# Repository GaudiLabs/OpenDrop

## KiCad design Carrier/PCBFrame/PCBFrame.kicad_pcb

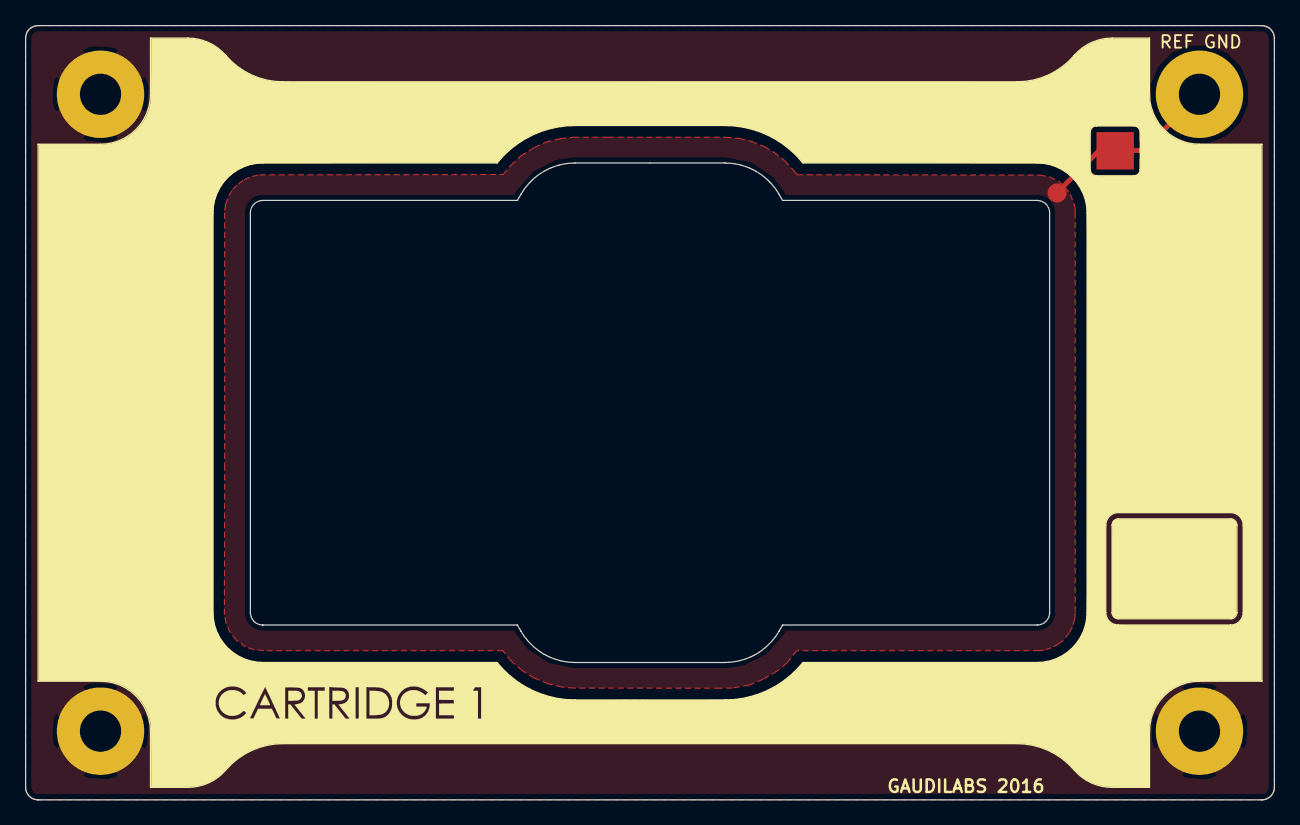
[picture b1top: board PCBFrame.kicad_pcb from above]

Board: 2 copper layers, 100.0 x 62.0 mm, 6 parts (0 on the bottom side), 2 nets.

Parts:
REF GND: MountPad3; MountingHoleRound3mm
X2, X3, X4: MountPad3; MountingHoleRound3mm
X5: MountPad3; Measurement_Point_Round-SMD-Pad_Small
X6: MountPad3; Measurement_Point_Square-SMD-Pad_Big

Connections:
GND: X2.1, X3.1, X4.1
GNDREF: REF GND.1, X5.1, X6.1

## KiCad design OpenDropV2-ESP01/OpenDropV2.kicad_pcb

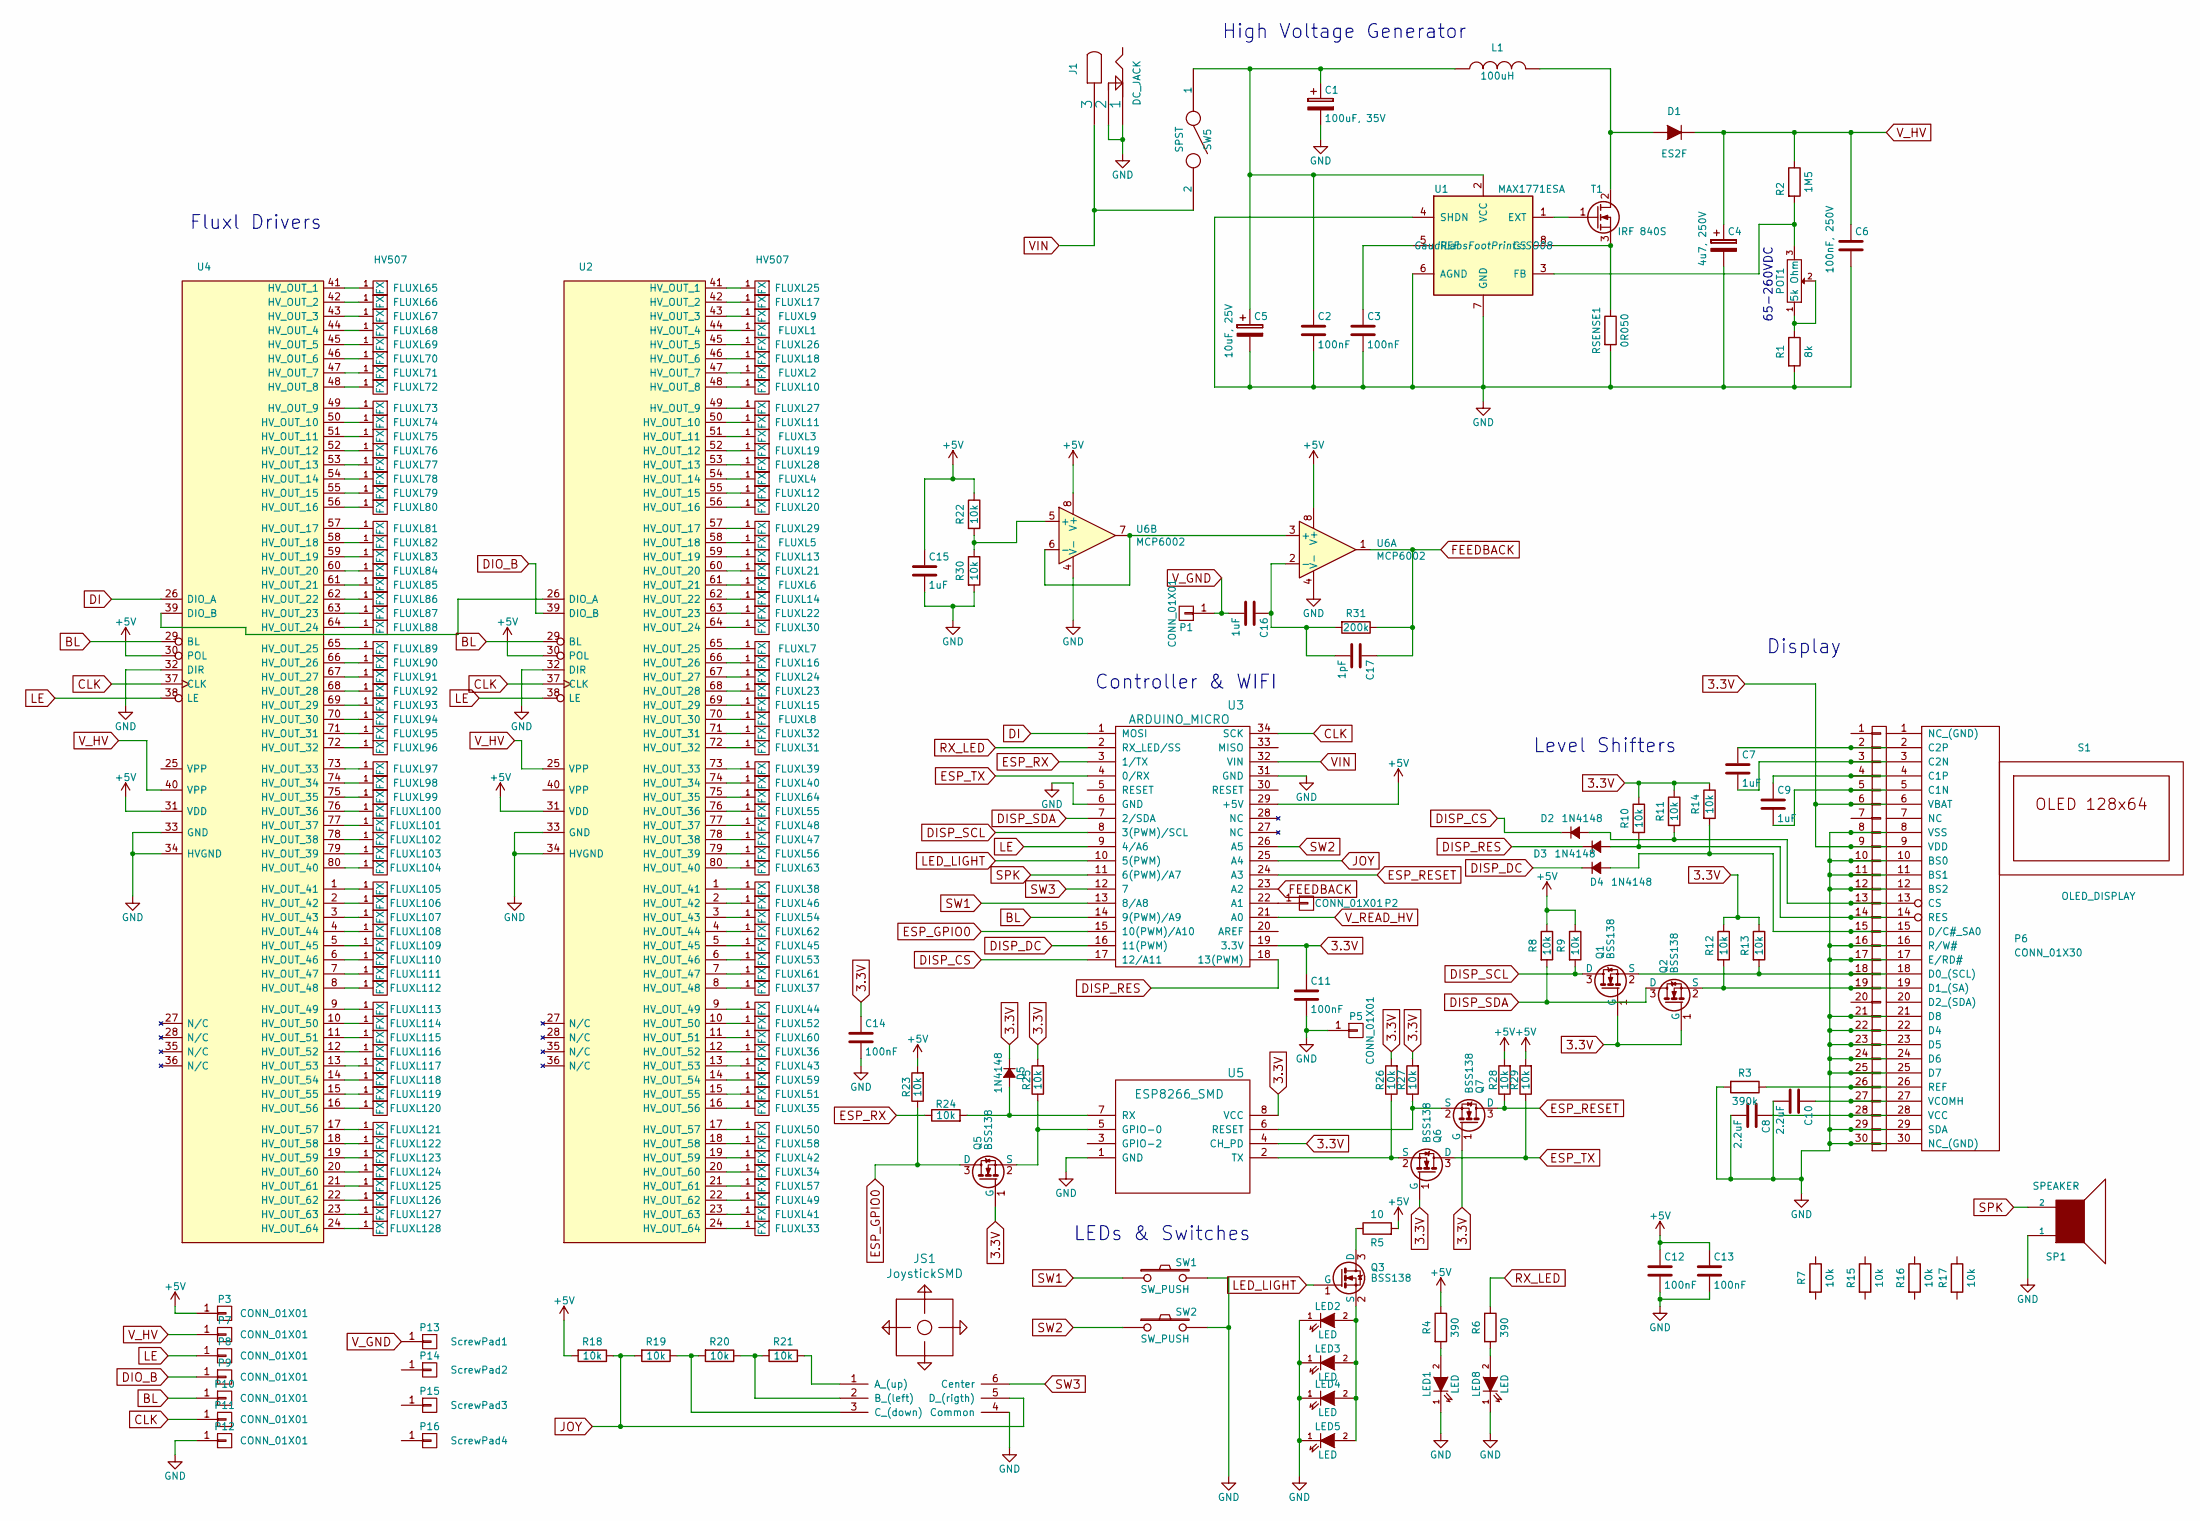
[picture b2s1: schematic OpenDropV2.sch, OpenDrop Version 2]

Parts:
C1: 100uF, 35V; R_2512_HandSoldering
C2, C3, C11, C12, C13, C14: 100nF; C_0805
C4: 4u7, 250V; C_SMD_12mm
C5: 10uF, 25V; C_1210_HandSoldering
C6: 100nF, 250V; C100n_250V
C7, C9, C15, C16: 1uF; C_0805
C8, C10: 2.2uF; C_0805
C17: 1pF; C_0805
D1: ES2F; DO-214AA
D2, D3, D4, D5: 1N4148; SOD-323
FLUXL1, FLUXL2, FLUXL3, FLUXL4, FLUXL5, FLUXL6, FLUXL7, FLUXL8, FLUXL9, FLUXL10, FLUXL11, FLUXL12, FLUXL13, FLUXL14, FLUXL15, FLUXL16, FLUXL17, FLUXL18, FLUXL19, FLUXL20, FLUXL21, FLUXL22, FLUXL23, FLUXL24, FLUXL25, FLUXL26, FLUXL27, FLUXL28, FLUXL29, FLUXL30, FLUXL31, FLUXL32, FLUXL33, FLUXL34, FLUXL35, FLUXL36, FLUXL37, FLUXL38, FLUXL39, FLUXL40, FLUXL41, FLUXL42, FLUXL43, FLUXL44, FLUXL45, FLUXL46, FLUXL47, FLUXL48, FLUXL49, FLUXL50, FLUXL51, FLUXL52, FLUXL53, FLUXL54, FLUXL55, FLUXL56, FLUXL57, FLUXL58, FLUXL59, FLUXL60, FLUXL61, FLUXL62, FLUXL63, FLUXL64, FLUXL65, FLUXL66, FLUXL67, FLUXL68, FLUXL69, FLUXL70, FLUXL71, FLUXL72, FLUXL73, FLUXL74, FLUXL75, FLUXL76, FLUXL77, FLUXL78, FLUXL79, FLUXL80, FLUXL81, FLUXL82, FLUXL83, FLUXL84, FLUXL85, FLUXL86, FLUXL87, FLUXL88, FLUXL89, FLUXL90, FLUXL91, FLUXL92, FLUXL93, FLUXL94, FLUXL95, FLUXL96, FLUXL97, FLUXL98, FLUXL99, FLUXL100, FLUXL101, FLUXL102, FLUXL103, FLUXL104, FLUXL105, FLUXL106, FLUXL107, FLUXL108, FLUXL109, FLUXL110, FLUXL111, FLUXL112, FLUXL113, FLUXL114, FLUXL115, FLUXL116, FLUXL117, FLUXL118, FLUXL119, FLUXL120, FLUXL121, FLUXL122, FLUXL123, FLUXL124, FLUXL125, FLUXL126, FLUXL127, FLUXL128: FX; FLUXPAD_2_75_4MIL_4_5
J1: DC_JACK; DC_JACK_SMD
JS1: JoystickSMD; JoystickSMD_SKQUSeries
L1: 100uH; Inductor_18.54x15.24
LED1, LED8: LED; LED-0805
LED2, LED3, LED4, LED5: LED; LED_SIDE
P1, P2, P3, P5, P7, P8, P9, P10, P11, P12: CONN_01X01; Measurement_Point_Square-SMD-Pad_Small
P6: CONN_01X30; OLED_SolderPads
P13: ScrewPad1; MountingHolePad_3x9mm
P14: ScrewPad2; MountingHolePad_3x9mm
P15: ScrewPad3; MountingHolePad_3x9mm
P16: ScrewPad4; MountingHolePad_3x9mm
POT1: 5k Ohm; Potentiometer_Trimmer-Suntan-TSR-3386P
Q1, Q2, Q3, Q5, Q6, Q7: BSS138; SOT-23
R1: 8k; R_0805
R2: 1M5; R_2512
R3: 390k; R_0805
R4, R6: 390; R_0805
R5: 10; R_0805
R7, R15, R16, R17: 10k; R_0805_HeatPad
R8, R9, R10, R11, R12, R13, R14, R18, R19, R20, R21, R22, R23, R24, R25, R26, R27, R28, R29, R30: 10k; R_0805
R31: 200k; R_0805
RSENSE1: 0R050; R_2010
S1: OLED_DISPLAY; OLED_096_1
SP1: SPEAKER; SMD_PA12_Piezzo
SW1, SW2: SW_PUSH; PUSH_BUTTON_SMD
SW5: SPST; Switch_On-On
T1: IRF 840S; D2PAK
U1: MAX1771ESA; SO08
U2, U4: HV507; PQFP-80_14x20mm_Pitch0.8mm
U3: ARDUINO_MICRO; ARDUINO_MICRO_SMD
U5: ESP8266_SMD
U6: MCP6002; SO08

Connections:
3.3V: C11.1, C14.1, D5.1 (K), P6.6, P6.9, Q1.1 (G), Q2.1 (G), Q5.1 (G), Q6.1 (G), Q7.1 (G), R10.1, R11.1, R12.1, R13.1, R14.1, R25.2, R26.2, R27.2, S1.6 (VBAT), S1.9 (VDD), U3.19 (3.3V), U5.4 (CH_PD), U5.8 (VCC)
CLK: P11.1, U2.37 (CLK), U3.34 (SCK), U4.37 (CLK)
DI: U3.1 (MOSI), U4.26 (DIO_A)
DIO_B: P9.1, U2.39 (DIO_B)
DISP_CS: D2.1 (K), U3.17 (12/A11)
DISP_DC: D4.1 (K), U3.16 (11(PWM))
DISP_RES: D3.1 (K), U3.18 (13(PWM))
DISP_SCL: Q1.3 (D), R9.2, U3.8 (3(PWM)/SCL)
DISP_SDA: Q2.3 (D), R8.2, U3.7 (2/SDA)
ESP_GPIO0: Q5.3 (D), R23.1, U3.15 (10(PWM)/A10)
ESP_RESET: Q7.3 (D), R28.1, U3.24 (A3)
ESP_RX: R24.1, U3.3 (1/TX)
ESP_TX: Q6.3 (D), R29.1, U3.4 (0/RX)
FEEDBACK: C17.1, R31.1, U3.23 (A2), U6.1
GND: C1.2, C2.2, C3.2, C4.2, C5.2, C6.2, C8.2, C10.2, C11.2, C12.2, C13.2, C14.2, C15.2, J1.1, J1.2, JS1.4 (Common), LED1.1 (K), LED2.1 (K), LED3.1 (K), LED4.1 (K), LED5.1 (K), LED8.1 (K), P5.1, P6.8, P6.10, P6.11, P6.12, P6.16, P6.17, P6.21, P6.22, P6.23, P6.24, P6.25, P6.29, P6.30, P12.1, R1.2, R3.2, R30.2, RSENSE1.2, S1.8 (VSS), S1.10 (BS0), S1.11 (BS1), S1.12 (BS2), S1.16 (R/W#), S1.17 (E/RD#), S1.21 (D8), S1.22 (D4), S1.23 (D5), S1.24 (D6), S1.25 (D7), S1.29 (SDA), S1.30 (NC_(GND)), SP1.1, SW1.2, SW2.2, U1.4 (SHDN), U1.6 (AGND), U1.7 (GND), U2.32 (DIR), U2.33 (GND), U2.34 (HVGND), U3.6 (GND), U3.31 (GND), U4.32 (DIR), U4.33 (GND), U4.34 (HVGND), U5.1 (GND), U6.4 (V-)
JOY: JS1.5 (D_(rigth)), R18.1, R19.2, U3.25 (A4)
LE: P8.1, U2.38 (LE), U3.9 (4/A6), U4.38 (LE)
LED_LIGHT: Q3.1 (G), U3.10 (5(PWM))
unnamed: C1.1, C2.1, C5.1, L1.1, SW5.1, U1.2 (VCC)
unnamed: C3.1, U1.5 (REF)
unnamed: C7.1, P6.2, S1.2 (C2P)
unnamed: C7.2, P6.3, S1.3 (C2N)
unnamed: C8.1, P6.28, S1.28 (VCC)
unnamed: C9.1, P6.4, S1.4 (C1P)
unnamed: C9.2, P6.5, S1.5 (C1N)
unnamed: C10.1, P6.27, S1.27 (VCOMH)
unnamed: C16.1, C17.2, R31.2, U6.2 (-)
unnamed: D1.2 (A), L1.2, T1.2 (D)
unnamed: D2.2 (A), P6.13, R11.2, S1.13 (CS)
unnamed: D3.2 (A), P6.14, R10.2, S1.14 (RES)
unnamed: D4.2 (A), P6.15, R14.2, S1.15 (D/C#_SA0)
unnamed: D5.2 (A), R24.2, U5.7 (RX)
unnamed: FLUXL1.1, U2.44 (HV_OUT_4)
unnamed: FLUXL2.1, U2.47 (HV_OUT_7)
unnamed: FLUXL3.1, U2.51 (HV_OUT_11)
unnamed: FLUXL4.1, U2.54 (HV_OUT_14)
unnamed: FLUXL5.1, U2.58 (HV_OUT_18)
unnamed: FLUXL6.1, U2.61 (HV_OUT_21)
unnamed: FLUXL7.1, U2.65 (HV_OUT_25)
unnamed: FLUXL8.1, U2.70 (HV_OUT_30)
unnamed: FLUXL9.1, U2.43 (HV_OUT_3)
unnamed: FLUXL10.1, U2.48 (HV_OUT_8)
unnamed: FLUXL11.1, U2.50 (HV_OUT_10)
unnamed: FLUXL12.1, U2.55 (HV_OUT_15)
unnamed: FLUXL13.1, U2.59 (HV_OUT_19)
unnamed: FLUXL14.1, U2.62 (HV_OUT_22)
unnamed: FLUXL15.1, U2.69 (HV_OUT_29)
unnamed: FLUXL16.1, U2.66 (HV_OUT_26)
unnamed: FLUXL17.1, U2.42 (HV_OUT_2)
unnamed: FLUXL18.1, U2.46 (HV_OUT_6)
unnamed: FLUXL19.1, U2.52 (HV_OUT_12)
unnamed: FLUXL20.1, U2.56 (HV_OUT_16)
unnamed: FLUXL21.1, U2.60 (HV_OUT_20)
unnamed: FLUXL22.1, U2.63 (HV_OUT_23)
unnamed: FLUXL23.1, U2.68 (HV_OUT_28)
unnamed: FLUXL24.1, U2.67 (HV_OUT_27)
unnamed: FLUXL25.1, U2.41 (HV_OUT_1)
unnamed: FLUXL26.1, U2.45 (HV_OUT_5)
unnamed: FLUXL27.1, U2.49 (HV_OUT_9)
unnamed: FLUXL28.1, U2.53 (HV_OUT_13)
unnamed: FLUXL29.1, U2.57 (HV_OUT_17)
unnamed: FLUXL30.1, U2.64 (HV_OUT_24)
unnamed: FLUXL31.1, U2.72 (HV_OUT_32)
unnamed: FLUXL32.1, U2.71 (HV_OUT_31)
unnamed: FLUXL33.1, U2.24 (HV_OUT_64)
unnamed: FLUXL34.1, U2.20 (HV_OUT_60)
unnamed: FLUXL35.1, U2.16 (HV_OUT_56)
unnamed: FLUXL36.1, U2.12 (HV_OUT_52)
unnamed: FLUXL37.1, U2.8 (HV_OUT_48)
unnamed: FLUXL38.1, U2.1 (HV_OUT_41)
unnamed: FLUXL39.1, U2.73 (HV_OUT_33)
unnamed: FLUXL40.1, U2.74 (HV_OUT_34)
unnamed: FLUXL41.1, U2.23 (HV_OUT_63)
unnamed: FLUXL42.1, U2.19 (HV_OUT_59)
unnamed: FLUXL43.1, U2.13 (HV_OUT_53)
unnamed: FLUXL44.1, U2.9 (HV_OUT_49)
unnamed: FLUXL45.1, U2.5 (HV_OUT_45)
unnamed: FLUXL46.1, U2.2 (HV_OUT_42)
unnamed: FLUXL47.1, U2.78 (HV_OUT_38)
unnamed: FLUXL48.1, U2.77 (HV_OUT_37)
unnamed: FLUXL49.1, U2.22 (HV_OUT_62)
unnamed: FLUXL50.1, U2.17 (HV_OUT_57)
unnamed: FLUXL51.1, U2.15 (HV_OUT_55)
unnamed: FLUXL52.1, U2.10 (HV_OUT_50)
unnamed: FLUXL53.1, U2.6 (HV_OUT_46)
unnamed: FLUXL54.1, U2.3 (HV_OUT_43)
unnamed: FLUXL55.1, U2.76 (HV_OUT_36)
unnamed: FLUXL56.1, U2.79 (HV_OUT_39)
unnamed: FLUXL57.1, U2.21 (HV_OUT_61)
unnamed: FLUXL58.1, U2.18 (HV_OUT_58)
unnamed: FLUXL59.1, U2.14 (HV_OUT_54)
unnamed: FLUXL60.1, U2.11 (HV_OUT_51)
unnamed: FLUXL61.1, U2.7 (HV_OUT_47)
unnamed: FLUXL62.1, U2.4 (HV_OUT_44)
unnamed: FLUXL63.1, U2.80 (HV_OUT_40)
unnamed: FLUXL64.1, U2.75 (HV_OUT_35)
unnamed: FLUXL65.1, U4.41 (HV_OUT_1)
unnamed: FLUXL66.1, U4.42 (HV_OUT_2)
unnamed: FLUXL67.1, U4.43 (HV_OUT_3)
unnamed: FLUXL68.1, U4.44 (HV_OUT_4)
unnamed: FLUXL69.1, U4.45 (HV_OUT_5)
unnamed: FLUXL70.1, U4.46 (HV_OUT_6)
unnamed: FLUXL71.1, U4.47 (HV_OUT_7)
unnamed: FLUXL72.1, U4.48 (HV_OUT_8)
unnamed: FLUXL73.1, U4.49 (HV_OUT_9)
unnamed: FLUXL74.1, U4.50 (HV_OUT_10)
unnamed: FLUXL75.1, U4.51 (HV_OUT_11)
unnamed: FLUXL76.1, U4.52 (HV_OUT_12)
unnamed: FLUXL77.1, U4.53 (HV_OUT_13)
unnamed: FLUXL78.1, U4.54 (HV_OUT_14)
unnamed: FLUXL79.1, U4.55 (HV_OUT_15)
unnamed: FLUXL80.1, U4.56 (HV_OUT_16)
unnamed: FLUXL81.1, U4.57 (HV_OUT_17)
unnamed: FLUXL82.1, U4.58 (HV_OUT_18)
unnamed: FLUXL83.1, U4.59 (HV_OUT_19)
unnamed: FLUXL84.1, U4.60 (HV_OUT_20)
unnamed: FLUXL85.1, U4.61 (HV_OUT_21)
unnamed: FLUXL86.1, U4.62 (HV_OUT_22)
unnamed: FLUXL87.1, U4.63 (HV_OUT_23)
unnamed: FLUXL88.1, U4.64 (HV_OUT_24)
unnamed: FLUXL89.1, U4.65 (HV_OUT_25)
unnamed: FLUXL90.1, U4.66 (HV_OUT_26)
unnamed: FLUXL91.1, U4.67 (HV_OUT_27)
unnamed: FLUXL92.1, U4.68 (HV_OUT_28)
unnamed: FLUXL93.1, U4.69 (HV_OUT_29)
unnamed: FLUXL94.1, U4.70 (HV_OUT_30)
unnamed: FLUXL95.1, U4.71 (HV_OUT_31)
unnamed: FLUXL96.1, U4.72 (HV_OUT_32)
unnamed: FLUXL97.1, U4.73 (HV_OUT_33)
unnamed: FLUXL98.1, U4.74 (HV_OUT_34)
unnamed: FLUXL99.1, U4.75 (HV_OUT_35)
unnamed: FLUXL100.1, U4.76 (HV_OUT_36)
unnamed: FLUXL101.1, U4.77 (HV_OUT_37)
unnamed: FLUXL102.1, U4.78 (HV_OUT_38)
unnamed: FLUXL103.1, U4.79 (HV_OUT_39)
unnamed: FLUXL104.1, U4.80 (HV_OUT_40)
unnamed: FLUXL105.1, U4.1 (HV_OUT_41)
unnamed: FLUXL106.1, U4.2 (HV_OUT_42)
unnamed: FLUXL107.1, U4.3 (HV_OUT_43)
unnamed: FLUXL108.1, U4.4 (HV_OUT_44)
unnamed: FLUXL109.1, U4.5 (HV_OUT_45)
unnamed: FLUXL110.1, U4.6 (HV_OUT_46)
unnamed: FLUXL111.1, U4.7 (HV_OUT_47)
unnamed: FLUXL112.1, U4.8 (HV_OUT_48)
unnamed: FLUXL113.1, U4.9 (HV_OUT_49)
unnamed: FLUXL114.1, U4.10 (HV_OUT_50)
unnamed: FLUXL115.1, U4.11 (HV_OUT_51)
unnamed: FLUXL116.1, U4.12 (HV_OUT_52)
unnamed: FLUXL117.1, U4.13 (HV_OUT_53)
unnamed: FLUXL118.1, U4.14 (HV_OUT_54)
unnamed: FLUXL119.1, U4.15 (HV_OUT_55)
unnamed: FLUXL120.1, U4.16 (HV_OUT_56)
unnamed: FLUXL121.1, U4.17 (HV_OUT_57)
unnamed: FLUXL122.1, U4.18 (HV_OUT_58)
unnamed: FLUXL123.1, U4.19 (HV_OUT_59)
unnamed: FLUXL124.1, U4.20 (HV_OUT_60)
unnamed: FLUXL125.1, U4.21 (HV_OUT_61)
unnamed: FLUXL126.1, U4.22 (HV_OUT_62)
unnamed: FLUXL127.1, U4.23 (HV_OUT_63)
unnamed: FLUXL128.1, U4.24 (HV_OUT_64)
unnamed: JS1.1 (A_(up)), R21.1
unnamed: JS1.2 (B_(left)), R20.1, R21.2
unnamed: JS1.3 (C_(down)), R19.1, R20.2
unnamed: LED1.2 (A), R4.2
unnamed: LED2.2 (A), LED3.2 (A), LED4.2 (A), LED5.2 (A), Q3.2 (S)
unnamed: LED8.2 (A), R6.2
unnamed: P2.1, U3.22 (A1)
unnamed: P6.18, Q1.2 (S), R13.2, S1.18 (D0_(SCL))
unnamed: P6.19, Q2.2 (S), R12.2, S1.19 (D1_(SA))
unnamed: P6.26, R3.1, S1.26 (REF)
unnamed: POT1.1, POT1.2, R1.1
unnamed: POT1.3, R2.2, U1.3 (FB)
unnamed: Q3.3 (D), R5.1
unnamed: Q5.2 (S), R25.1, U5.5 (GPIO-0)
unnamed: Q6.2 (S), R26.1, U5.2 (TX)
unnamed: Q7.2 (S), R27.1, U5.6 (RESET)
unnamed: R22.2, R30.1, U6.5 (+)
unnamed: RSENSE1.1, T1.3 (S), U1.8 (CS)
unnamed: T1.1 (G), U1.1 (EXT)
unnamed: U2.26 (DIO_A), U4.39 (DIO_B)
unnamed: U6.3 (+), U6.6 (-), U6.7
RX_LED: R6.1, U3.2 (RX_LED/SS)
SPK: SP1.2, U3.11 (6(PWM)/A7)
SW1: SW1.1, U3.13 (8/A8)
SW2: SW2.1, U3.26 (A5)
SW3: JS1.6 (Center), U3.12 (7)
VIN: J1.3, SW5.2, U3.32 (VIN)
V_GND: C16.2, P1.1, P13.1
V_HV: C4.1, C6.1, D1.1 (K), P7.1, R2.1, U2.25 (VPP), U4.40 (VPP)

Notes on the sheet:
65-260VDC
High Voltage Generator
Fluxl Drivers
Controller & WIFI
Display
Level Shifters
LEDs & Switches

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
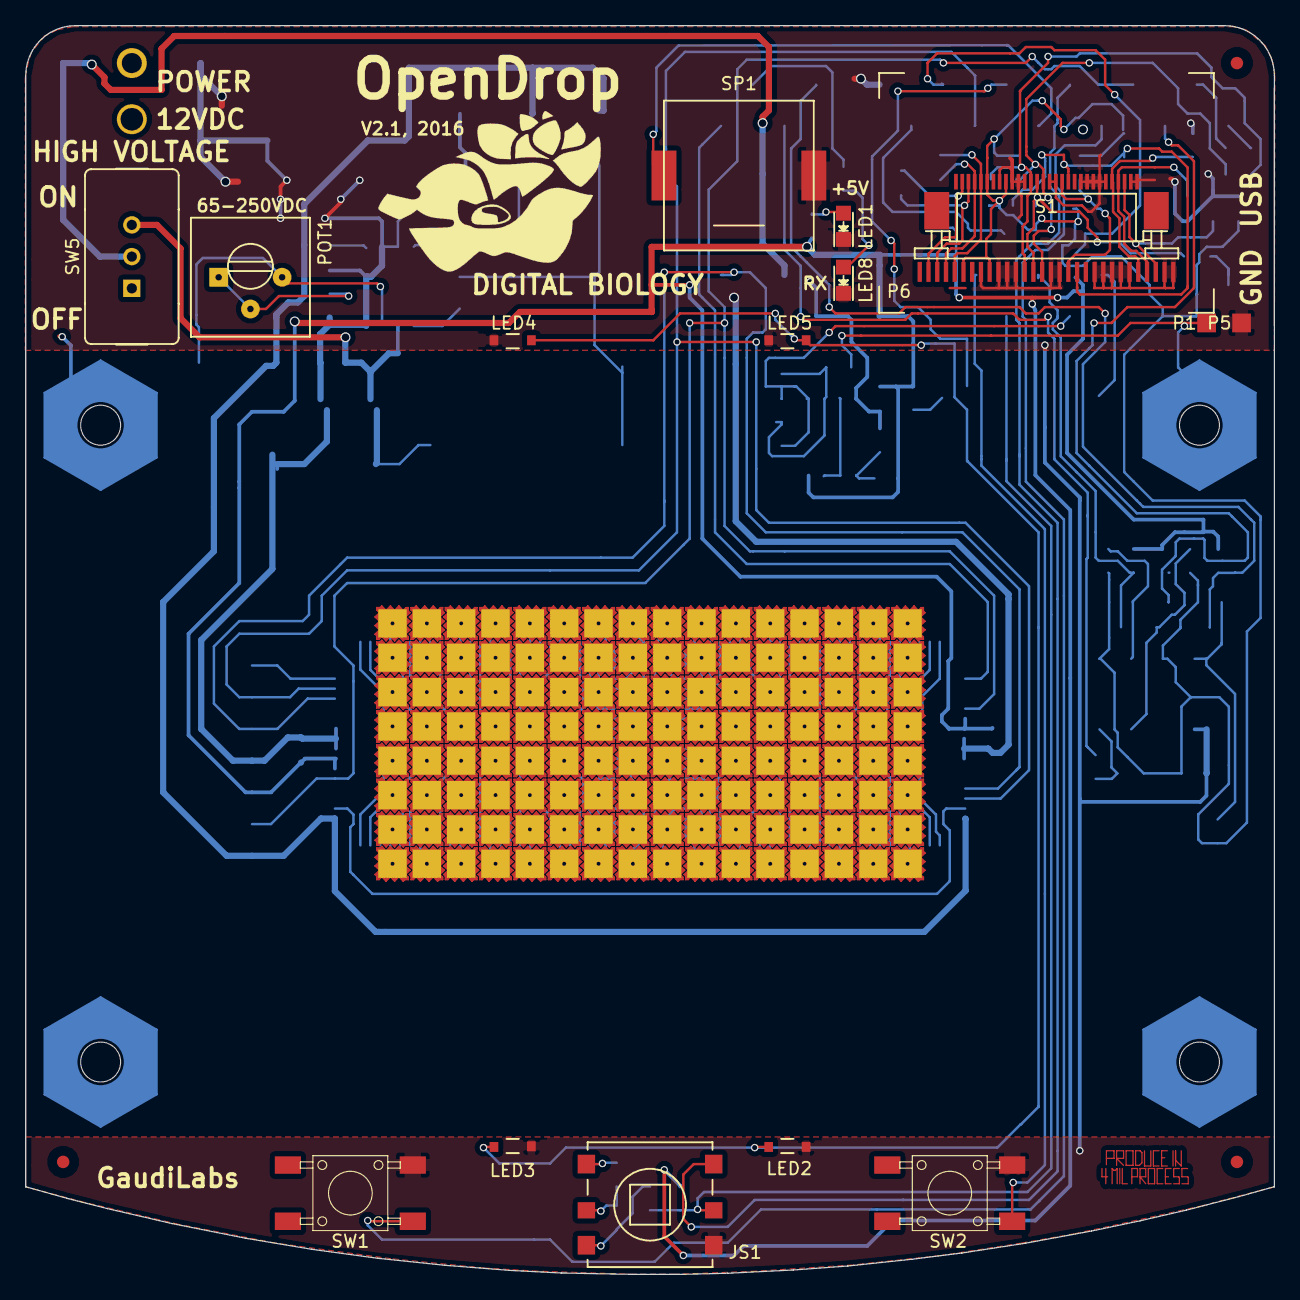
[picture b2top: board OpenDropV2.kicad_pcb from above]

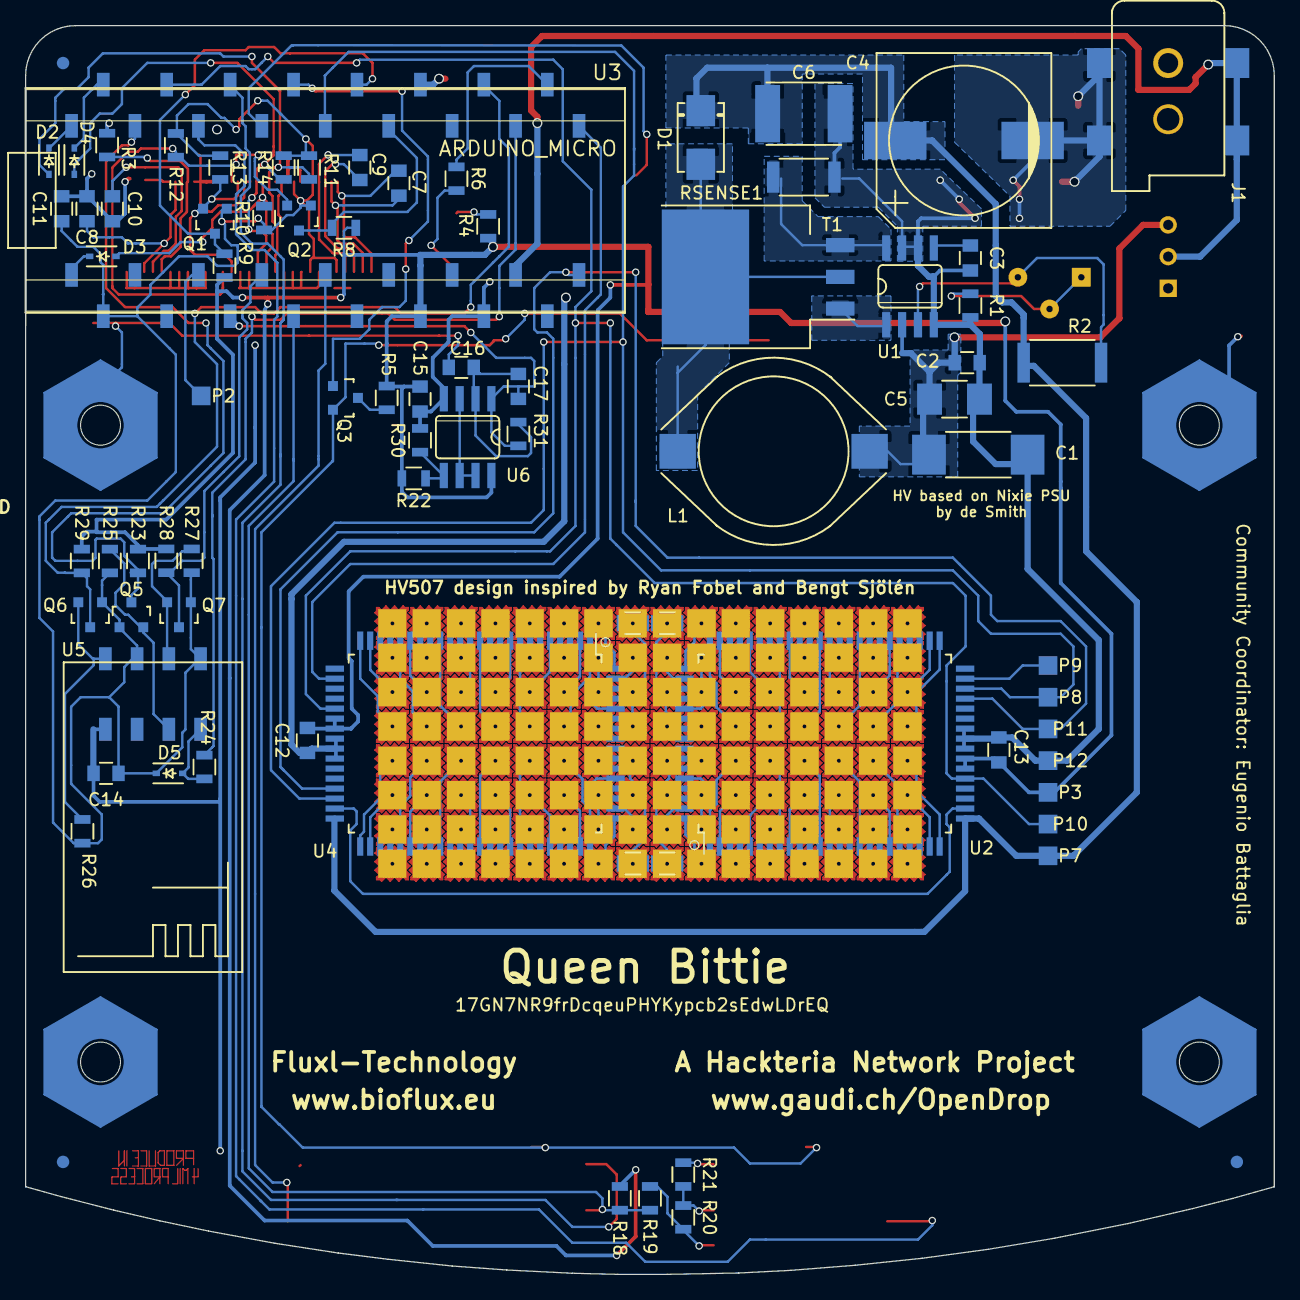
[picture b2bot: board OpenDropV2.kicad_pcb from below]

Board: 2 copper layers, 100.0 x 100.0 mm, 225 parts (77 on the bottom side), 191 nets.

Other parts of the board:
P13#2, P13#3, P13#4: ScrewPad1; MountingHolePad_3x9mm
